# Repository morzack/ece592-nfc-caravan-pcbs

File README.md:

# ece592-nfc-caravan-pcbs

submodules vendor in reference boards for tt06 and caravel.

most up-to-date caravel evaluation PCB at `caravel_board/hardware/development/caravel-dev-v5-M.2` -- this contains details on FTDI module and flash memory for bringup of on-chip VexRiscv management CPU

## work breakdown

following a top-down design

1. make symbol for pinout (actual)
2. identify routing constaints for breakout
3. make block diagram of off-chip requirements for bringup
4. implement schematics for off-chip stuff
5. layout, etc

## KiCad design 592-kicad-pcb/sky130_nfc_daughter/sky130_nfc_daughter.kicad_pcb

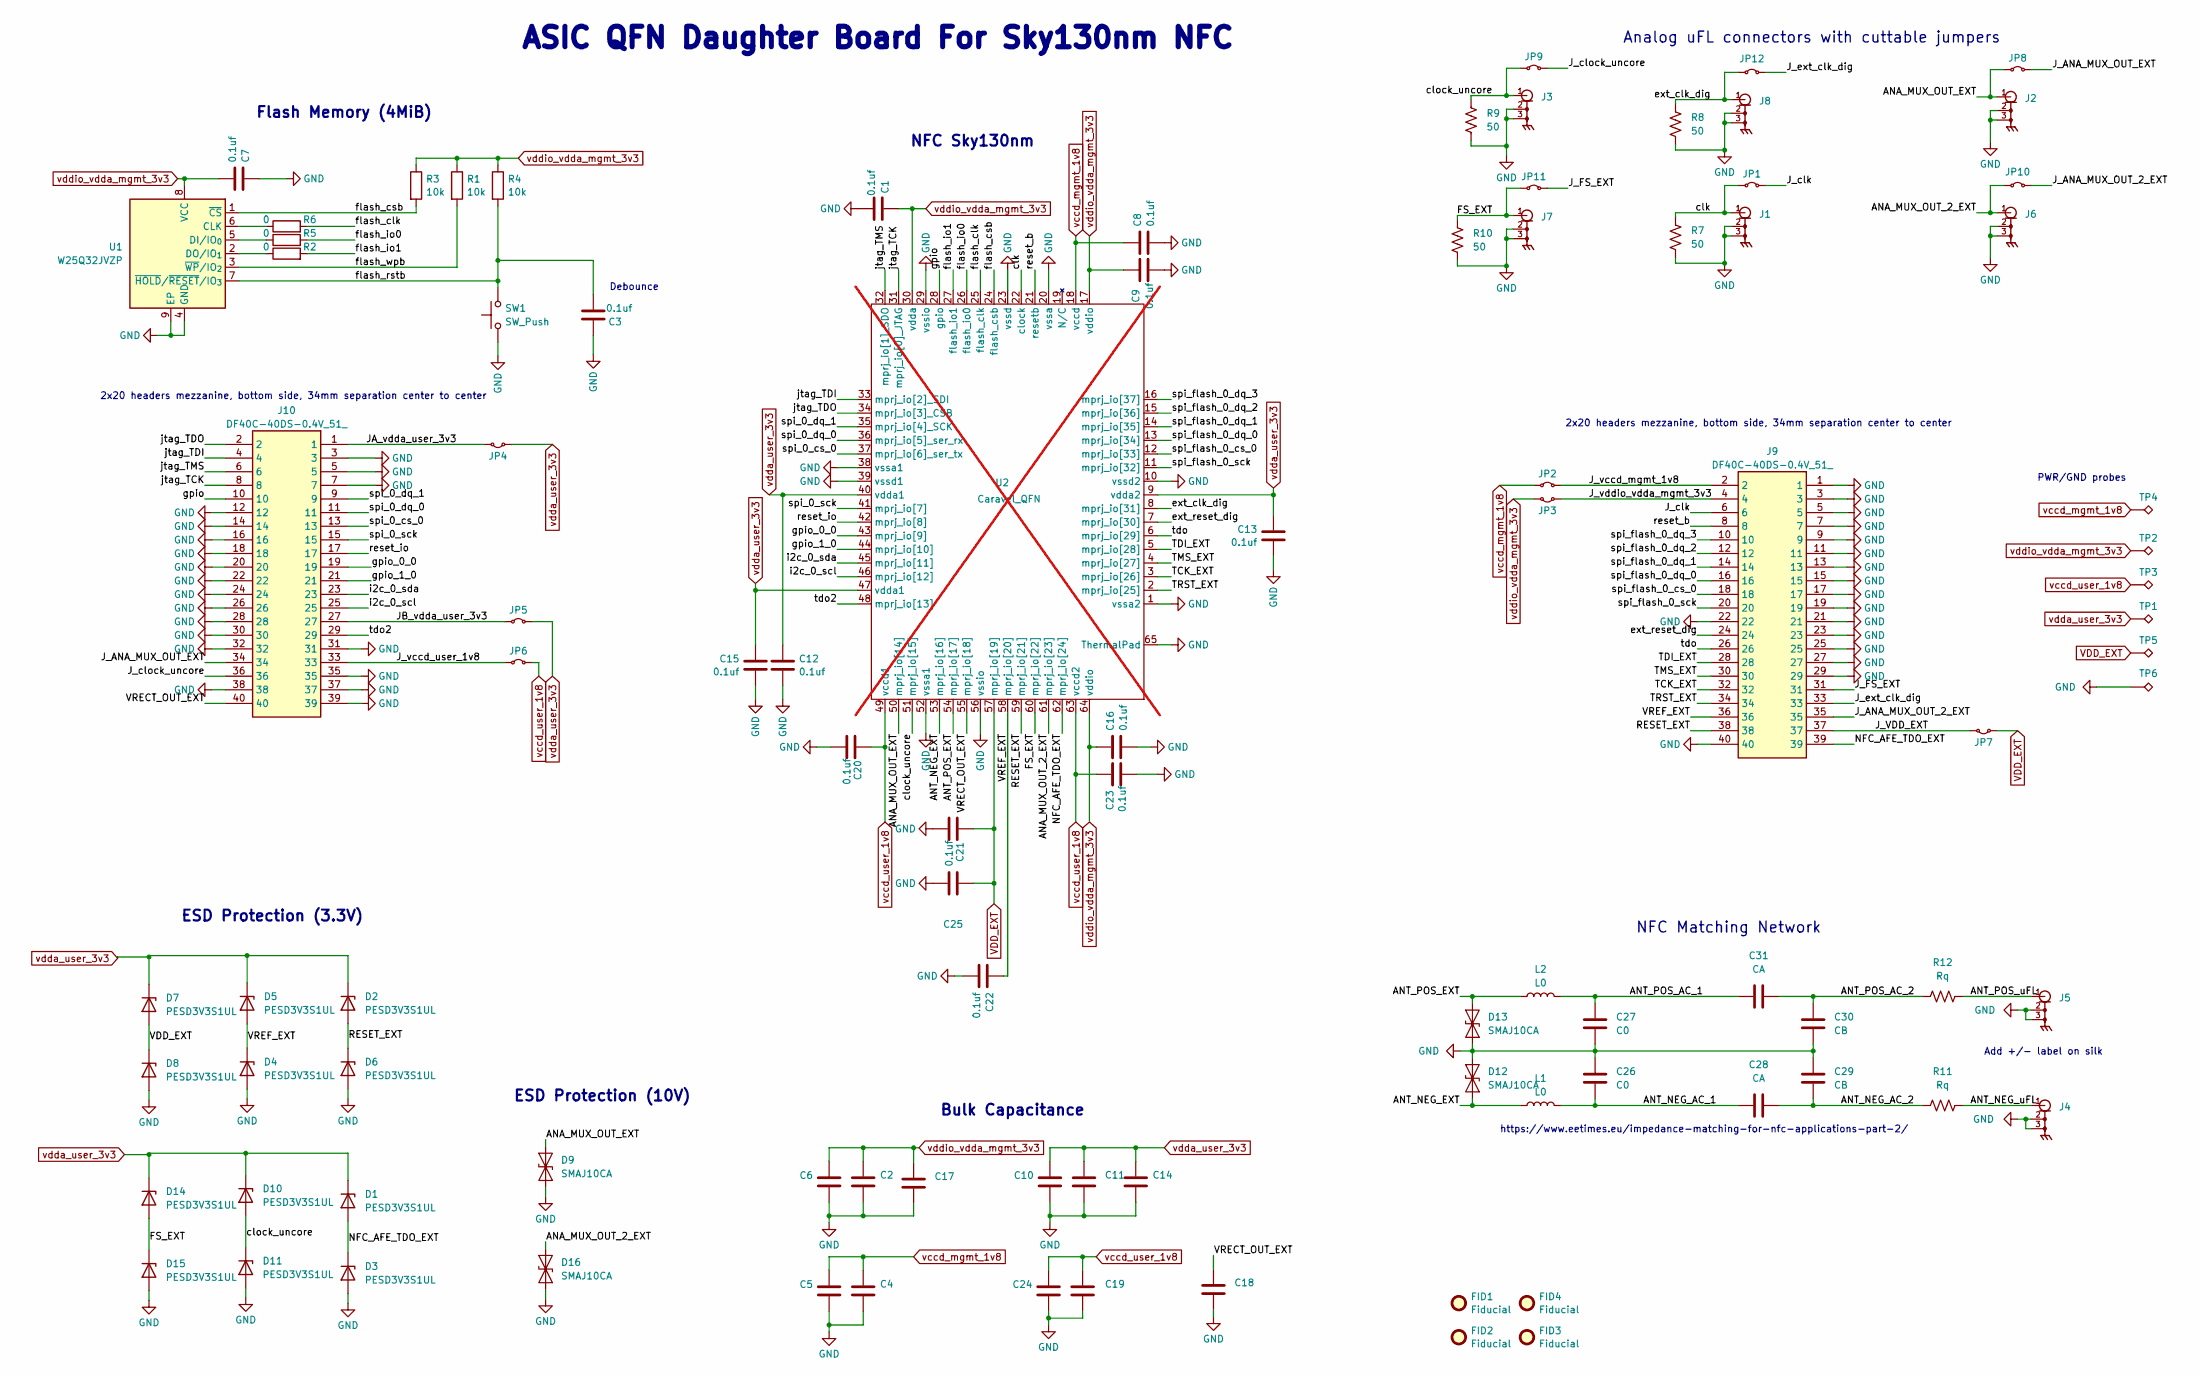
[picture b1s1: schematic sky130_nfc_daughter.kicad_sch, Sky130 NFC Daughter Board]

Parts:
C1, C3, C7, C8, C9, C12, C13, C15, C16, C20, C21, C22, C23: 0.1uf; C_0402_1005Metric
C2, C4, C5, C6, C10, C11, C14, C17, C18, C19, C24, C25: C_1u_0603_50V; C_0603_1608Metric
C26, C27: C0; C_0603_1608Metric_Pad1.08x0.95mm_HandSolder
C28, C31: CA; C_0603_1608Metric_Pad1.08x0.95mm_HandSolder
C29, C30: CB; C_0603_1608Metric_Pad1.08x0.95mm_HandSolder
D1, D2, D3, D4, D5, D6, D7, D8, D10, D11, D14, D15: PESD3V3S1UL; D_SOD-882
D9, D12, D13, D16: SMAJ10CA; D_SMA
FID1, FID2, FID3, FID4: Fiducial; Fiducial_1mm_Mask2mm
J1, J2, J3, J4, J5, J6, J7, J8: U.FL-R-SMT-1_80_; UFLRSMT180
J9, J10: DF40C-40DS-0.4V_51_; DF40C40DS04V51
JP1, JP2, JP3, JP4, JP5, JP6, JP7, JP8, JP9, JP10, JP11, JP12: Jumper_2_Small_Bridged; SolderJumper-2_P1.3mm_Bridged_RoundedPad1.0x1.5mm
L1, L2: L0; L_0603_1608Metric_Pad1.05x0.95mm_HandSolder
R1, R3, R4: 10k; R_0402_1005Metric
R2, R5, R6: 0; R_0402_1005Metric
R7, R8, R9, R10: 50; R_0402_1005Metric
R11, R12: Rq; R_0603_1608Metric_Pad0.98x0.95mm_HandSolder
SW1: SW_Push; SW_Push_1P1T_XKB_TS-1187A
TP1, TP2, TP3, TP4, TP5, TP6: TestPoint_Alt; TestPoint_Keystone_5019_Minature; MPN 5019; DigikeyPN 36-5019CT-ND
U1: W25Q32JVZP; WSON-8-1EP_6x5mm_P1.27mm_EP3.4x4.3mm
U2: Caravel_QFN; QFN-64-1EP_9x9mm_P0.5mm_EP7.65x7.65mm_SMALL_EPAD; not fitted

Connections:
/ANA_MUX_OUT_2_EXT: D16.2 (A2), J6.1, JP10.1 (A), U2.61 (mprj_io[23])
/ANA_MUX_OUT_EXT: D9.2 (A2), J2.1, JP8.1 (A), U2.50 (mprj_io[14])
/ANT_NEG_AC_1: C26.2, C28.1, L1.2
/ANT_NEG_AC_2: C28.2, C29.2, R11.1
/ANT_NEG_EXT: D12.2 (A2), L1.1, U2.53 (mprj_io[16])
/ANT_NEG_uFL: J4.1, R11.2
/ANT_POS_AC_1: C27.1, C31.1, L2.2
/ANT_POS_AC_2: C30.1, C31.2, R12.1
/ANT_POS_EXT: D13.2 (A2), L2.1, U2.54 (mprj_io[17])
/ANT_POS_uFL: J5.1, R12.2
/FS_EXT: D14.2 (A), D15.1 (K), J7.1, JP11.1 (A), R10.2, U2.60 (mprj_io[22])
/JA_vdda_user_3v3: J10.1, JP4.1 (A)
/JB_vdda_user_3v3: J10.27, JP5.2 (B)
/J_ANA_MUX_OUT_2_EXT: J9.35, JP10.2 (B)
/J_ANA_MUX_OUT_EXT: J10.34, JP8.2 (B)
/J_FS_EXT: J9.31, JP11.2 (B)
/J_VDD_EXT: J9.37, JP7.1 (A)
/J_clk: J9.6, JP1.2 (B)
/J_clock_uncore: J10.36, JP9.2 (B)
/J_ext_clk_dig: J9.33, JP12.2 (B)
/J_vccd_mgmt_1v8: J9.2, JP2.1 (A)
/J_vccd_user_1v8: J10.33, JP6.2 (B)
/J_vddio_vdda_mgmt_3v3: J9.4, JP3.1 (A)
/NFC_AFE_TDO_EXT: D1.2 (A), D3.1 (K), J9.39, U2.62 (mprj_io[24])
/RESET_EXT: D2.2 (A), D6.1 (K), J9.38, U2.59 (mprj_io[21])
/TCK_EXT: J9.32, U2.3 (mprj_io[26])
/TDI_EXT: J9.28, U2.5 (mprj_io[28])
/TMS_EXT: J9.30, U2.4 (mprj_io[27])
/TRST_EXT: J9.34, U2.2 (mprj_io[25])
/VRECT_OUT_EXT: C18.1, J10.40, U2.55 (mprj_io[18])
/VREF_EXT: C22.1, D4.1 (K), D5.2 (A), J9.36, U2.58 (mprj_io[20])
/clk: J1.1, JP1.1 (A), R7.2, U2.22 (clock)
/clock_uncore: D10.2 (A), D11.1 (K), J3.1, JP9.1 (A), R9.2, U2.51 (mprj_io[15])
/ext_clk_dig: J8.1, JP12.1 (A), R8.2, U2.8 (mprj_io[31])
/ext_reset_dig: J9.24, U2.7 (mprj_io[30])
/flash_clk: R6.2, U2.25 (flash_clk)
/flash_csb: R3.2, U1.1 (~CS), U2.24 (flash_csb)
/flash_io0: R5.2, U2.26 (flash_io0)
/flash_io1: R2.2, U2.27 (flash_io1)
/flash_rstb: C3.1, R4.2, SW1.2, U1.7 (~HOLD/~RESET/IO_{3})
/flash_wpb: R1.2, U1.3 (~WP/IO_{2})
/gpio: J10.10, U2.28 (gpio)
/gpio_0_0: J10.19, U2.43 (mprj_io[9])
/gpio_1_0: J10.21, U2.44 (mprj_io[10])
/i2c_0_scl: J10.25, U2.46 (mprj_io[12])
/i2c_0_sda: J10.23, U2.45 (mprj_io[11])
/jtag_TCK: J10.8, U2.31 (mprj_io[0]_JTAG)
/jtag_TDI: J10.4, U2.33 (mprj_io[2]_SDI)
/jtag_TDO: J10.2, U2.34 (mprj_io[3]_CSB)
/jtag_TMS: J10.6, U2.32 (mprj_io[1]_SDO)
/reset_b: J9.8, U2.21 (resetb)
/reset_io: J10.17, U2.42 (mprj_io[8])
/spi_0_cs_0: J10.13, U2.37 (mprj_io[6]_ser_tx)
/spi_0_dq_0: J10.11, U2.36 (mprj_io[5]_ser_rx)
/spi_0_dq_1: J10.9, U2.35 (mprj_io[4]_SCK)
/spi_0_sck: J10.15, U2.41 (mprj_io[7])
/spi_flash_0_cs_0: J9.18, U2.12 (mprj_io[33])
/spi_flash_0_dq_0: J9.16, U2.13 (mprj_io[34])
/spi_flash_0_dq_1: J9.14, U2.14 (mprj_io[35])
/spi_flash_0_dq_2: J9.12, U2.15 (mprj_io[36])
/spi_flash_0_dq_3: J9.10, U2.16 (mprj_io[37])
/spi_flash_0_sck: J9.20, U2.11 (mprj_io[32])
/tdo: J9.26, U2.6 (mprj_io[29])
/tdo2: J10.29, U2.48 (mprj_io[13])
GND: C1.1, C2.2, C3.2, C4.2, C5.2, C6.2, C7.1, C8.1, C9.1, C10.2, C11.2, C12.2, C13.1, C14.2, C15.2, C16.1, C17.2, C18.2, C19.2, C20.2, C21.2, C22.2, C23.1, C24.2, C25.1, C26.1, C27.2, C29.1, C30.2, D3.2 (A), D4.2 (A), D6.2 (A), D8.2 (A), D9.1 (A1), D11.2 (A), D12.1 (A1), D13.1 (A1), D15.2 (A), D16.1 (A1), J1.2, J1.3, J2.2, J2.3, J3.2, J3.3, J4.2, J4.3, J5.2, J5.3, J6.2, J6.3, J7.2, J7.3, J8.2, J8.3, J9.1, J9.3, J9.5, J9.7, J9.9, J9.11, J9.13, J9.15, J9.17, J9.19, J9.21, J9.22, J9.23, J9.25, J9.27, J9.29, J9.40, J10.3, J10.5, J10.7, J10.12, J10.14, J10.16, J10.18, J10.20, J10.22, J10.24, J10.26, J10.28, J10.30, J10.31, J10.32, J10.35, J10.37, J10.38, J10.39, R7.1, R8.1, R9.1, R10.1, SW1.1, TP6.1, U1.4 (GND), U1.9 (EP), U2.1 (vssa2), U2.10 (vssd2), U2.20 (vssa), U2.23 (vssd), U2.29 (vssio), U2.38 (vssa1), U2.39 (vssd1), U2.52 (vssa1), U2.56 (vssio), U2.65 (ThermalPad); also elsewhere on the board
unnamed: R6.1, U1.6 (CLK)
unnamed: R5.1, U1.5 (DI/IO_{0})
unnamed: R2.1, U1.2 (DO/IO_{1})
VDD_EXT: C21.1, C25.2, D7.2 (A), D8.1 (K), JP7.2 (B), TP5.1, U2.57 (mprj_io[19])
vccd_mgmt_1v8: C4.1, C5.1, C8.2, JP2.2 (B), TP4.1, U2.18 (vccd)
vccd_user_1v8: C19.1, C20.1, C23.2, C24.1, JP6.1 (A), TP3.1, U2.49 (vccd1), U2.63 (vccd2)
vdda_user_3v3: C10.1, C11.1, C12.1, C13.2, C14.1, C15.1, D1.1 (K), D2.1 (K), D5.1 (K), D7.1 (K), D10.1 (K), D14.1 (K), JP4.2 (B), JP5.1 (A), TP1.1, U2.9 (vdda2), U2.40 (vdda1), U2.47 (vdda1)
vddio_vdda_mgmt_3v3: C1.2, C2.1, C6.1, C7.2, C9.2, C16.2, C17.1, JP3.2 (B), R1.1, R3.1, R4.1, TP2.1, U1.8 (VCC), U2.17 (vddio), U2.30 (vdda), U2.64 (vddio)

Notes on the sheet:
ESD Protection (10V)
2x20 headers mezzanine, bottom side, 34mm separation center to center
https://www.eetimes.eu/impedance-matching-for-nfc-applications-part-2/
ASIC QFN Daughter Board For Sky130nm NFC
NFC Sky130nm
PWR/GND probes
Flash Memory (4MiB)
Debounce
Bulk Capacitance
NFC Matching Network
ESD Protection (3.3V)
Analog uFL connectors with cuttable jumpers
Add +/- label on silk

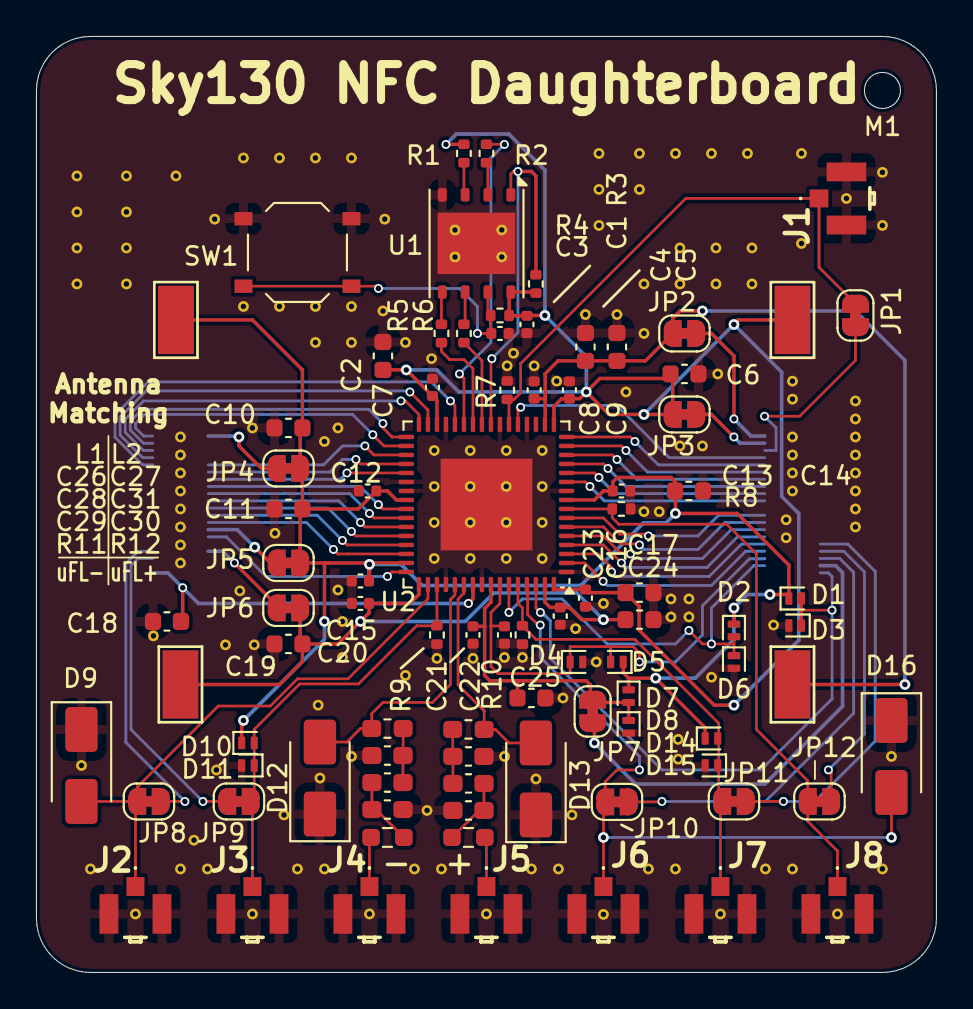
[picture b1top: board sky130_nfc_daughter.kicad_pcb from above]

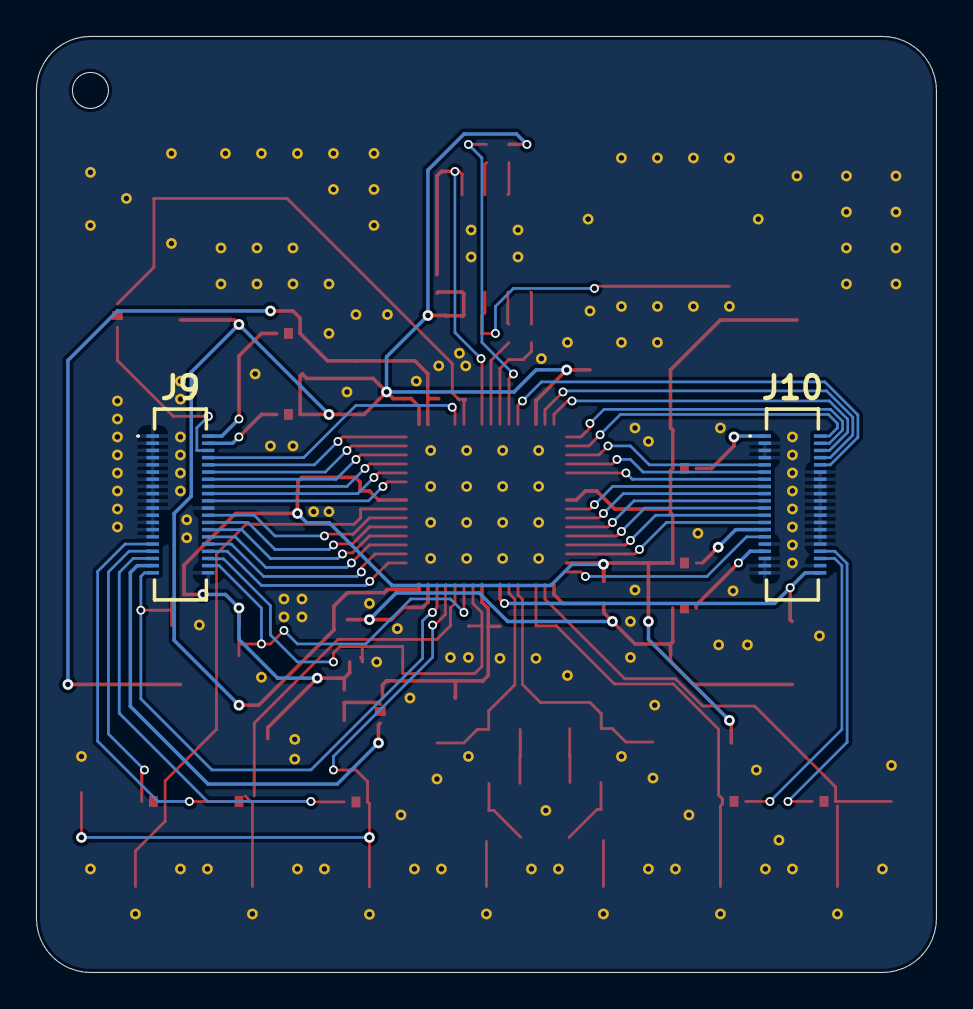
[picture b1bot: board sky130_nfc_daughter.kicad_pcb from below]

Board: 4 copper layers, 50.0 x 52.0 mm, 96 parts (2 on the bottom side), 73 nets.

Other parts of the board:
M1: MountingHole_2mm
STITCHM1, STITCHM2, STITCHM3, STITCHM4, STITCHM5: STITCHING_VIA_0p3mm

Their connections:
GND: STITCHM1.1, STITCHM2.1, STITCHM3.1, STITCHM4.1, STITCHM5.1; also elsewhere on the board

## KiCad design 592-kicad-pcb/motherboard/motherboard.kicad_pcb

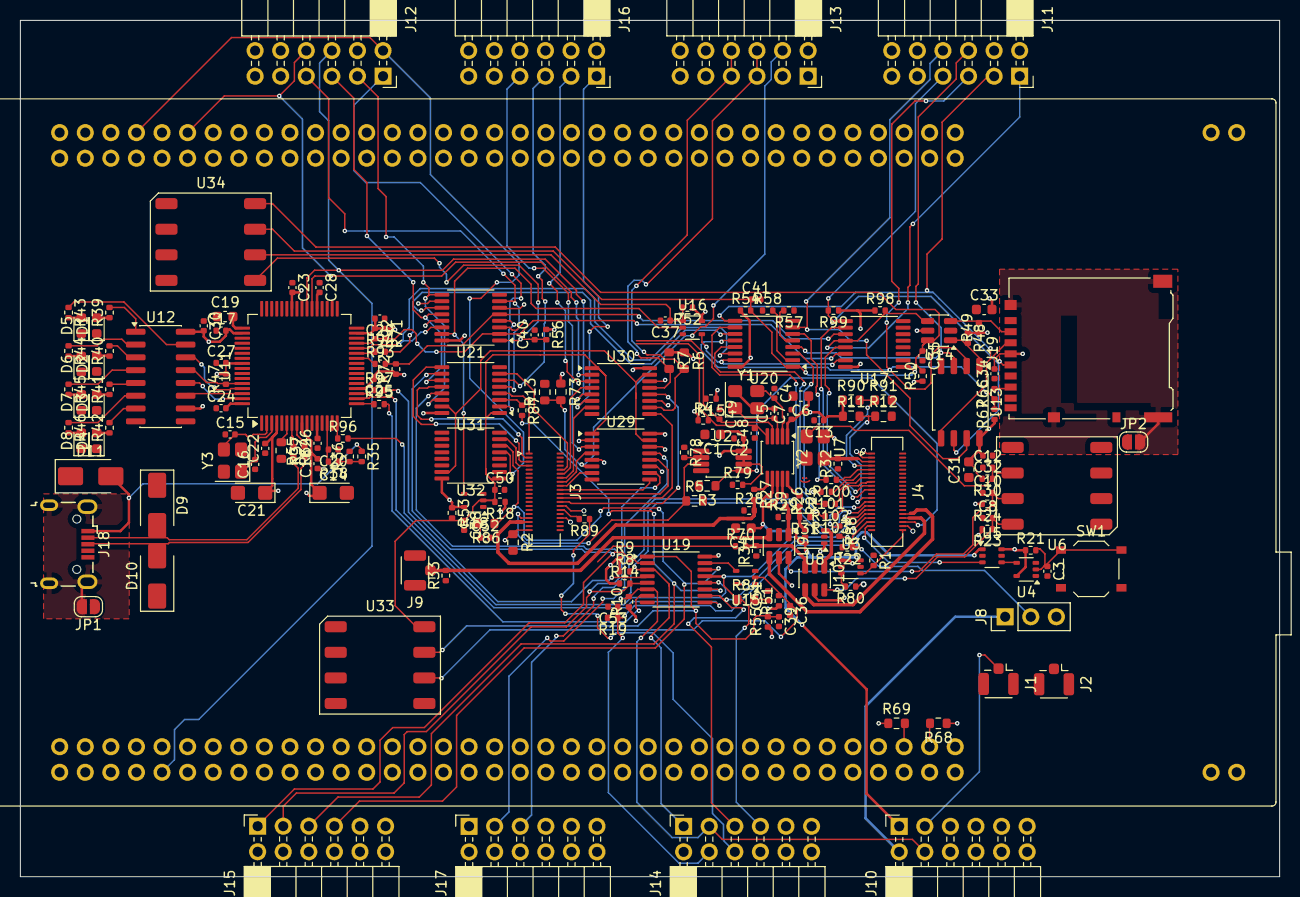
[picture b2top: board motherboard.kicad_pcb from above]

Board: 4 copper layers, 125.0 x 85.0 mm, 194 parts (0 on the bottom side), 176 nets.

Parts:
C1, C6, C11, C31, C33: 1u; C_0603_1608Metric
C2, C3, C7, C8, C9, C10, C12, C17, C18, C22, C23, C24, C25, C26, C27, C28, C29, C30, C32, C34, C35, C36, C37, C38, C39, C40, C41, C50: 100n; C_0402_1005Metric
C4, C5: 16p; C_0402_1005Metric
C13, C20, C53: 10n; C_0402_1005Metric
C14, C21: 4.7u; CP_EIA-3216-18_Kemet-A
C15, C16: 10p; C_0402_1005Metric
C19: 3.3u; C_0603_1608Metric
C48, C49: 0; C_0402_1005Metric
C51, C52: 100p; C_0402_1005Metric
D1, D2, D3, D4: d_white; D_0603_1608Metric
D5, D6, D7, D8: d_red; D_0603_1608Metric
D9, D10, D11: SMAJ10CA; D_SMA
J1, J2, J9: U.FL; U.FL_Hirose_U.FL-R-SMT-1_Vertical
J3, J4: DF40C-40DP-0.4V(51); Hirose_DF40C(2.0)-40DS-0.4V_2x20_P0.4mm
J8: 2.54mm jumper; PinHeader_1x03_P2.54mm_Vertical
J10, J11, J12, J13, J14, J15, J16, J17: Conn_02x06_Odd_Even; PinSocket_2x06_P2.54mm_Horizontal
J18: USB_B_Micro; USB_Micro-B_Wuerth_629105150521
J19: Micro_SD_Card; microSD_HC_Hirose_DM3AT-SF-PEJM5
JP1, JP2: solderjump; SolderJumper-2_P1.3mm_Open_RoundedPad1.0x1.5mm
R1: 1M; R_0402_1005Metric
R2, R3, R5: 10M; R_0603_1608Metric
R4, R15: 5k; R_0402_1005Metric
R6, R7: 2k; R_0603_1608Metric
R8, R9, R10, R14, R18, R19, R21, R23, R24, R28, R29, R30, R31, R32, R33, R34, R36, R47, R50, R51, R52, R53, R54, R55, R56, R57, R58, R67, R71, R72, R92, R98, R99: 10k; R_0402_1005Metric
R11, R12, R13, R73, R90, R91: 10k; R_0603_1608Metric
R22, R48, R49: 100k; R_0402_1005Metric
R25, R26, R27: 10; R_0402_1005Metric
R35: 4.7k; R_0402_1005Metric
R37: 12k <1%; R_0603_1608Metric
R38: 1k; R_0402_1005Metric
R39, R40, R41, R42: 150; R_0402_1005Metric
R43, R44, R45, R46: 330; R_0402_1005Metric
R64, R65, R70, R87, R88, R89, R100, R101, R102, R103: 0; R_0402_1005Metric
R66: 27; R_0402_1005Metric
R68, R69: 5k; R_0603_1608Metric
R78, R79, R80: 100; R_0402_1005Metric
R84, R86: 75; R_0603_1608Metric
R93, R94, R95, R96, R97: 22; R_0402_1005Metric
SW1: C318884; SW_Push_1P1T_XKB_TS-1187A
U1: NUCLEO144-H743ZI; ST_Morpho_Connector_144_STLink
U2: OPA2328DGKR; VSSOP-8_3x3mm_P0.65mm
U3, U5, U8: 74LVC1T45GW; SOT-363_SC-70-6
U4, U15, U18: SN74LVC1G14DBV; SOT-353_SC-70-5
U6, U33, U34: SMXS-04K; SMXS-04K-TP
U7: SX3M10.000B10F20TNN; Crystal_SMD_3225-4Pin_3.2x2.5mm
U9, U10, U14: SN74LVC1G3157DBVR; SOT-23-6
U11: FT4232H; LQFP-64_10x10mm_P0.5mm
U12: 74HC595; SOIC-16_3.9x9.9mm_P1.27mm
U13: W25Q32JVSS; SOIC-8_5.3x5.3mm_P1.27mm
U16: SN74LVC1G00DCK; SOT-353_SC-70-5
U17, U19, U20, U21, U29, U30, U31, U32: 74CBTLV3257PW,118; TSSOP-16_4.4x5mm_P0.65mm
Y1: NX3225GA-25.000M-STD-CRG-2; Crystal_SMD_3225-4Pin_3.2x2.5mm
Y2: Si5351A; MSOP-10_3x3mm_P0.5mm
Y3: X322512MSB4SI; Crystal_SMD_3225-4Pin_3.2x2.5mm

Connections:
+1V8: C9.1, C11.1, J10.1, U3.6 (VCCB), U5.1 (VCCA), U8.6 (VCCB), Y2.7 (VDDO)
+3V3: C1.1, C2.1, C6.1, C7.1, C13.1, C14.1, C17.2, C18.2, C21.1, C22.2, C23.2, C25.2, C27.2, C29.2, C30.2, C31.2, C32.2, C33.2, C34.2, J10.11, J10.12, J11.11, J11.12, J12.11, J12.12, J13.11, J13.12, J14.11, J14.12, J15.11, J15.12, J16.11, J16.12, J17.11, J17.12, J19.4 (VDD), R4.1, R6.1, R7.1, R8.1, R9.1, R10.1, R11.1, R14.1, R15.1, R18.1, R21.1, R23.2, R24.2, R30.2, R47.2, R48.1, R49.1, R50.1, R51.1, R52.1, R53.1, R54.1, R55.1, R56.1, R67.1, R68.1, R69.1, R71.1, R72.1, R73.1, R90.1, R92.1, R98.1, R99.1, U2.8 (Vdd), U3.1 (VCCA), U4.5 (VCC), U5.6 (VCCB), U7.4 (VDD), U8.1 (VCCA), U9.5 (VCC), U10.5 (VCC), U11.4 (VPHY), U11.9 (VPLL), U11.20 (VCCIO), U11.31 (VCCIO), U11.42 (VCCIO), U11.50 (VREGIN), U11.56 (VCCIO), U12.10 (~SRCLR), U12.16 (VCC), U13.8 (VCC), U14.5 (VCC), U15.5 (VCC), U16.5 (VCC), U17.16 (VCC), U18.5 (VCC), U19.16 (VCC), U20.16 (VCC), U21.16 (VCC), U29.16 (VCC), U30.16 (VCC), U31.16 (VCC), U32.16 (VCC), Y2.1 (VDD)
/PA0_UART4_RX: U1.28 (PA0), U11.48 (DDBUS0)
/PA1_UART4_TX: U1.30 (ETH_REF_CLK/PA1), U11.52 (DDBUS1)
/PA4_DAC_OUT1: J8.3, U1.32 (PA4)
/PB8_I2C4_SCL: C49.2, R15.2, R68.2, U1.75 (PB8), Y2.4 (SCL)
/PB9_I2C4_SDA: C48.2, R4.2, R69.2, U1.77 (PB9), Y2.5 (SDA)
/PB14_TIM12_CH1: R70.1, U1.100 (LD3/PB14)
/PD7: U1.45 (PD7), U30.14
/PE0_UART8_RX: J12.6, U1.136 (PE0), U11.39 (CDBUS1), U30.5
/PE1_UART8_TX: J12.8, U1.61 (PE1), U11.38 (CDBUS0), U30.2
/PF6_SPI5_CS: U1.9 (PF6), U21.3
/PF7_SPI5_SCK: U1.11 (PF7), U21.6
/PF8_SPI5_MISO: U1.54 (PF8), U21.13
/PF9_SPI5_MOSI: U1.56 (PF9), U21.10
/PG0: U1.59 (PG0), U29.14
/PG1: U1.58 (PG1), U30.11
/PG9: U1.63 (PG9), U29.11
/PG10: U1.66 (PG10), U29.2
/PG12: J12.2, U1.65 (PG12), U32.5
/PG15: U1.64 (PG15), U29.5
/motherboard_top/ADC_chip_ana_mux_out_1: J1.1 (In), J10.3, R78.1
/motherboard_top/ADC_chip_ana_mux_out_2: J2.1 (In), J10.5, R79.1
/motherboard_top/GPIO_JTAG_FTDI_source_select: C39.1, R55.2, U19.1 (S), U33.7 (2o)
/motherboard_top/GPIO_MGMT_enable: C38.1, C50.1, R18.2, R53.2, U18.2, U29.1 (S), U30.1 (S), U31.1 (S), U32.1 (S), U33.8 (1o)
/motherboard_top/GPIO_SPI_MGMT_source_sel: C40.1, R56.2, U21.1 (S), U34.5 (4o)
/motherboard_top/GPIO_chip_nfc_afe_tdo_ext: J10.7, R80.1
/motherboard_top/GPIO_chip_nfc_ext_reset_dig: J4.23, J10.6, R11.2, R12.1
/motherboard_top/GPIO_chip_nfc_jtag_tdo: J14.5, R88.2, U19.10
/motherboard_top/GPIO_chip_nfc_jtag_tdo2: J14.6, R89.1
/motherboard_top/GPIO_chip_rck_reset_io: J13.4, R13.1, R73.2, U29.6
/motherboard_top/GPIO_ftdi_jtag_src_en: C36.1, R51.2, U15.2, U33.6 (3o)
/motherboard_top/GPIO_rck_mem_sel_sdB: C35.1, R50.2, U14.6 (S), U34.8 (1o)
/motherboard_top/GPIO_rck_mem_source_en: C37.1, R52.2, U16.1, U34.6 (3o)
/motherboard_top/GPIO_rck_mem_source_sel_ftdiB: C41.1, R54.2, U17.1 (S), U20.1 (S), U34.7 (2o)
/motherboard_top/ana_buffers/a1: R78.2, U2.1 (Vout1), U2.2 (Vin1m)
/motherboard_top/ana_buffers/a2: R79.2, U2.6 (Vin2m), U2.7 (Vout2)
/motherboard_top/anamisc_vref_ext_in: J8.1, J10.2
/motherboard_top/chip_connection/mprj_io_0: J3.7, U32.7
/motherboard_top/chip_connection/mprj_io_1: J3.5, U31.9
/motherboard_top/chip_connection/mprj_io_2: J3.3, U31.12
/motherboard_top/chip_connection/mprj_io_3: J3.1, U31.4
/motherboard_top/chip_connection/mprj_io_4: J3.10, U31.7
/motherboard_top/chip_connection/mprj_io_5: J3.12, U30.4
/motherboard_top/chip_connection/mprj_io_6: J3.14, U30.7
/motherboard_top/chip_connection/mprj_io_7: J3.16, U29.4
/motherboard_top/chip_connection/mprj_io_8: J3.18, U29.7
/motherboard_top/chip_connection/mprj_io_9: J3.20, U29.9
/motherboard_top/chip_connection/mprj_io_10: J3.22, U29.12
/motherboard_top/chip_connection/mprj_io_11: J3.24, U30.9
/motherboard_top/chip_connection/mprj_io_12: J3.26, U30.12
/motherboard_top/chip_connection/resetb: J4.7, R90.2, R91.1
/motherboard_top/chip_connection/user_3v3: J3.2, J3.28
/motherboard_top/chip_nfc_ana_mux_out: J3.33, R5.1, U2.3 (Vin1p)
/motherboard_top/chip_nfc_ana_mux_out_2: J4.36, R3.1, U2.5 (Vin2p)
/motherboard_top/chip_nfc_ext_clk_dig: J4.34, U10.4 (A)
/motherboard_top/chip_nfc_fs: J4.32, U9.4 (A)
/motherboard_top/chip_nfc_jtag_tck: J4.31, J14.7, R84.1, U19.13
/motherboard_top/chip_nfc_jtag_tdi: J4.27, J10.4, J14.3, R10.2, U19.6
/motherboard_top/chip_nfc_jtag_tms: J4.29, J14.1, R8.2, U19.3
/motherboard_top/chip_nfc_jtag_trst: C53.1, J4.33, J14.4, R19.1
/motherboard_top/chip_nfc_nfc_afe_tdo: J4.40, R1.2, U3.4 (B)
/motherboard_top/chip_nfc_reset: J4.37, U5.3 (A)
/motherboard_top/chip_nfc_vrect_out: J3.39, J10.8, R2.1
/motherboard_top/chip_nfc_vref: J4.35, J8.2, R22.1
/motherboard_top/chip_rck_clock_uncore: J3.35, R27.2, R28.2
/motherboard_top/chip_rck_gpio_0_0: J17.5, U29.10
/motherboard_top/chip_rck_gpio_1_0: J17.3, U29.13
/motherboard_top/chip_rck_i2c_scl: J13.5, J13.6, R7.2, U30.13
/motherboard_top/chip_rck_i2c_sda: J13.7, J13.8, R6.2, U30.10
/motherboard_top/chip_rck_jtag_tck: J15.7, R86.1, U19.14, U32.6
/motherboard_top/chip_rck_jtag_tdi: J15.3, R14.2, U19.5, U31.13
/motherboard_top/chip_rck_jtag_tdo: J15.5, R87.2, U19.11
/motherboard_top/chip_rck_jtag_tms: J15.1, R9.2, U19.2, U31.10
/motherboard_top/chip_rck_spi_0_cs_0: J16.1, U30.6
/motherboard_top/chip_rck_spi_0_dq_0_mosi: J16.3, U30.3
/motherboard_top/chip_rck_spi_0_dq_1_miso: J16.5, U31.6
/motherboard_top/chip_rck_spi_0_sck: J16.7, U29.3
/motherboard_top/chip_spi_flash_0_cs_0: J4.17, U17.13
/motherboard_top/chip_spi_flash_0_dq_0: R103.2, U20.10
/motherboard_top/chip_spi_flash_0_dq_1: R102.2, U20.13
/motherboard_top/chip_spi_flash_0_dq_2: R101.2, U20.3
/motherboard_top/chip_spi_flash_0_dq_3: R100.2, U20.6
/motherboard_top/chip_spi_flash_0_sck: J4.19, U17.10
/motherboard_top/chip_support_misc/GPIO_RESET_EXT: C3.1, R21.2, SW1.1 (A), U4.2
/motherboard_top/clock_sources/CARAVEL_CLK_EN: C12.2, R30.1, U6.6 (3o), U7.1 (OE)
/motherboard_top/clock_sources/EXT_CLK_DIG_SEL: C8.2, R23.1, U6.8 (1o), U10.6 (S)
/motherboard_top/clock_sources/FS_EXT_SEL: C10.2, R24.1, U6.7 (2o), U9.6 (S)
/motherboard_top/clock_sources/ext_clk_dig_gen: R25.2, R31.2, U8.4 (B)
/motherboard_top/clock_sources/fs_ext_aux: J9.1 (In), R33.2, U9.3 (B1)
/motherboard_top/clock_sources/fs_ext_gen: R26.2, R29.2, U9.1 (B2)
/motherboard_top/ftdi1_jtag_tck: R96.2, U19.12
/motherboard_top/ftdi1_jtag_tdi: R95.2, U19.7
/motherboard_top/ftdi1_jtag_tdo: U11.18 (ADBUS2), U19.9
/motherboard_top/ftdi1_jtag_tms: R97.2, U19.4
/motherboard_top/ftdi/FTDI_RESETb: C20.2, R38.2, U11.14 (~RESET)
/motherboard_top/ftdi/USB_DM: D9.2 (A2), J18.2 (D-), R64.2
/motherboard_top/ftdi/USB_DP: D10.2 (A2), J18.3 (D+), R65.1
/motherboard_top/ftdi/ftdi_1v8: C19.2, C24.2, C26.2, C28.2, U11.12 (VCORE), U11.37 (VCORE), U11.49 (VREGOUT), U11.64 (VCORE)
/motherboard_top/ftdi/ftdi_eeclk: U11.62 (EECLK), U12.11 (SRCLK)
/motherboard_top/ftdi/ftdi_eecs: U11.63 (EECS), U12.12 (RCLK)
/motherboard_top/ftdi/ftdi_eedata: U11.61 (EEDATA), U12.14 (SER)
/motherboard_top/ftdi/ftdi_pwren: R47.1, U11.60 (~PWREN), U12.13 (~OE)
/motherboard_top/ftdi_jtag_src_enB: U15.4, U19.15 (~OE)
/motherboard_top/ftdi_spi_cs: R71.2, R92.2, U11.29 (BDBUS3), U17.14, U21.2
/motherboard_top/ftdi_spi_miso: U11.28 (BDBUS2), U20.14, U21.14
/motherboard_top/ftdi_spi_mosi: R94.2, U20.11, U21.11
/motherboard_top/ftdi_spi_sck: R72.2, R93.2, U17.11, U21.5
/motherboard_top/memory/nor_cs: R48.2, U13.1 (~CS), U14.1 (B2)
/motherboard_top/memory/sd_cs: J19.2 (DAT3/CD), R49.2, U14.3 (B1)
/motherboard_top/mgmt_clk: J4.5, R32.2, U7.3 (OUT)
/motherboard_top/mgmt_csb: J12.1, U21.4, U31.2
/motherboard_top/mgmt_sck: J12.7, U21.7, U31.5
/motherboard_top/mgmt_sdi: J12.3, U21.9, U31.14
/motherboard_top/mgmt_sdo: J12.5, U21.12, U31.11
/motherboard_top/rck_mem_cs: J11.1, R98.2, U14.4 (A), U17.12
/motherboard_top/rck_mem_io2: J11.6, U13.3 (~WP/IO_{2}), U20.4
/motherboard_top/rck_mem_io3: J11.8, U13.7 (~HOLD/~RESET/IO_{3}), U20.7
/motherboard_top/rck_mem_miso_i01: J11.5, R66.1, R67.2, U13.2 (DO/IO_{1}), U20.12
/motherboard_top/rck_mem_mosi_io0: J11.3, J19.3 (CMD), U13.5 (DI/IO_{0}), U20.9
/motherboard_top/rck_mem_sck: J11.7, J19.5 (CLK), R99.2, U13.6 (CLK), U17.9
/motherboard_top/rck_mem_source_enB: U16.4, U17.15 (~OE), U20.15 (~OE)
/motherboard_top/spi_mgmt_enb: U16.2, U18.4, U21.15 (~OE)
GND: C1.2, C2.2, C3.2, C4.1, C5.2, C6.2, C7.2, C8.1, C9.2, C10.1, C11.2, C12.1, C13.2, C14.2, C15.1, C16.1, C17.1, C18.1, C19.1, C20.1, C21.2, C22.1, C23.1, C24.1, C25.1, C26.1, C27.1, C28.1, C29.1, C30.1, C31.1, C32.1, C33.1, C34.1, C35.2, C36.2, C37.2, C38.2, C39.2, C40.2, C41.2, C48.1, C49.1, C50.2, C51.2, C52.2, C53.2, D1.1 (K), D2.1 (K), D3.1 (K), D4.1 (K), D5.1 (K), D6.1 (K), D7.1 (K), D8.1 (K), D9.1 (A1), D10.1 (A1), D11.1 (A1), J1.2 (Ext), J2.2 (Ext), J3.4, J3.6, J3.8, J3.11, J3.13, J3.15, J3.17, J3.19, J3.21, J3.23, J3.25, J3.27, J3.29, J3.31, J3.32, J3.36, J3.37, J3.38, J3.40, J4.2, J4.4, J4.6, J4.8, J4.10, J4.12, J4.14, J4.16, J4.18, J4.20, J4.21, J4.22, J4.24, J4.26, J4.28, J4.30, J4.39, J9.2 (Ext), J10.9, J10.10, J11.9, J11.10, J12.9, J12.10, J13.2, J13.9, J13.10, J14.9, J14.10, J15.9, J15.10, J16.9, J16.10, J17.9, J17.10, J18.5 (GND), J19.6 (VSS), JP1.1 (A), JP2.1 (A), R1.1, R2.2, R3.2, R5.2, R12.2, R13.2, R19.2, R22.2, R28.1, R29.1, R31.1, R32.1, R33.1, R34.1, R36.2, R37.2, R57.1, R58.1, R91.2, SW1.2 (B), U1.8 (GND), U1.19 (GND), U1.20 (GND), U1.22 (GND), U1.49 (GND), U1.60 (GND), U1.71 (GND), U1.72 (GND), U1.81 (GND), U1.92 (GND), U1.104 (AGND), U1.111 (GND), U1.126 (GND), U1.135 (GND), U1.143 (GND), U1.144 (GND), U2.4 (Vss), U3.2 (GND), U3.5 (DIR), U4.3 (GND), U5.2 (GND), U5.5 (DIR), U6.1 (1i), U6.2 (2i), U6.3 (3i), U6.4 (4i), U6.5 (4o), U7.2 (GND), U8.2 (GND), U8.5 (DIR), U9.2 (GND), U10.2 (GND), U11.1 (GND), U11.5 (GND), U11.10 (AGND), U11.11 (GND), U11.13 (TEST), U11.15 (GND), U11.25 (GND), U11.35 (GND), U11.47 (GND), U11.51 (GND), U12.8 (GND), U13.4 (GND), U14.2 (GND), U15.3 (GND), U16.3 (GND), U17.8 (GND), U18.3 (GND), U19.8 (GND), U20.8 (GND), U21.8 (GND), U29.8 (GND), U30.8 (GND), U31.8 (GND), U32.8 (GND), U33.1 (1i), U33.2 (2i), U33.3 (3i), U33.4 (4i), U34.1 (1i), U34.2 (2i), U34.3 (3i), U34.4 (4i), Y1.2, Y1.4, Y2.8 (GND), Y3.2, Y3.4
unnamed: C51.1, R84.2
unnamed: C52.1, R86.2
unnamed: D1.2 (A), R39.1
unnamed: D2.2 (A), R40.1
unnamed: D3.2 (A), R41.1
unnamed: D4.2 (A), R42.1
unnamed: D5.2 (A), R43.2
unnamed: D6.2 (A), R44.2
unnamed: D7.2 (A), R45.2
unnamed: D8.2 (A), R46.2
unnamed: J3.30, R89.2
unnamed: J4.9, R100.1
unnamed: J4.11, R101.1
unnamed: J4.13, R102.1
unnamed: J4.15, R103.1
unnamed: J4.25, R88.1
unnamed: J18.6 (Shield), JP1.2 (B)
unnamed: J19.7 (DAT0), R66.2
unnamed: J19.11 (SHIELD), JP2.2 (B)
unnamed: R35.2, R36.1, R38.1
unnamed: R57.2, U20.5
unnamed: R58.2, U20.2
unnamed: R87.1, U31.3
unnamed: R80.2, U3.3 (A)
unnamed: U4.4, U5.4 (B)
unnamed: R34.2, R70.2, U10.3 (B1)
unnamed: U8.3 (A), U10.1 (B2)
unnamed: R96.1, U11.16 (ADBUS0)
unnamed: R95.1, U11.17 (ADBUS1)
unnamed: R97.1, U11.19 (ADBUS3)
unnamed: R93.1, U11.26 (BDBUS0)
unnamed: R94.1, U11.27 (BDBUS1)
unnamed: R64.1, U11.7 (DM)
unnamed: R65.2, U11.8 (DP)
unnamed: C15.2, U11.2 (OSCI), Y3.3
unnamed: C16.2, U11.3 (OSCO), Y3.1
unnamed: R37.1, U11.6 (REF)
unnamed: R43.1, U12.15 (QA)
unnamed: R39.2, U12.1 (QB)
unnamed: R44.1, U12.2 (QC)
unnamed: R40.2, U12.3 (QD)
unnamed: R45.1, U12.4 (QE)
unnamed: R41.2, U12.5 (QF)
unnamed: R46.1, U12.6 (QG)
unnamed: R42.2, U12.7 (QH)
unnamed: U29.15 (~OE), U30.15 (~OE), U31.15 (~OE), U32.15 (~OE)
unnamed: R25.1, Y2.10 (CLK0)
unnamed: R26.1, Y2.9 (CLK1)
unnamed: R27.1, Y2.6 (CLK2)
unnamed: C4.2, Y1.3, Y2.2 (XA)
unnamed: C5.1, Y1.1, Y2.3 (XB)
VBUS: D11.2 (A2), J18.1 (VBUS), R35.1

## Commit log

2025-10-02 submodule in open source boards
2025-10-02 add packaging/pin border pdf
2025-10-08 add symbol/footprint libs for project
2025-10-08 add hierarchy demo for clock sources
2025-10-08 add schematic for clock generator, some symbols
2025-10-09 update signal supporting ckts
2025-10-10 clean up supporting blocks; add nucleo symbol
2025-10-15 Init daughter board
2025-10-20 move daughterboard to subprj folder
2025-10-20 add footprints for signal conditioning
2025-10-22 update motheboard schems to include conn
2025-10-22 in-class work at schems
2025-10-23 clean up some pull up/downs
2025-10-24 add jlc stackup, size pulldowns
2025-10-25 rough layout stufF
2025-10-26 add mezzanine symbol/footprint, init daughterboard placement
2025-10-26 daughter placement v1, add 3D models for mezzanine + uFL
2025-10-26 update uFL 3D model
2025-10-27 Added most of nucleo domain to the motherboard schematic
2025-10-27 resaved maybe more updates on the motherboard schematic
2025-10-27 Added the irq and irq2 inputs to the nucleo
2025-10-27 Added the rest of the ports
2025-10-27 add 3D models with rel paths, add stitching via footprint, update daughter pcb schematic
2025-10-27 begin routing daughterboard
2025-10-31 clean up schematics, add proper connectors
2025-11-01 update ftdi chip
2025-11-01 combine hierarchy of all sans power
2025-11-01 add some daughterboard routing
2025-11-02 more daughterboard routing
2025-11-03 scoreboard! scoreboard! wait... what?
2025-11-03 current monitor symbol
2025-11-03 daughterboard routing, changed some mezzanine pins - more to come
2025-11-03 partial update to use STM board, updated muxing of FTDI
2025-11-03 working through switching
2025-11-05 pmic switching schem done
2025-11-05 update FTDI interfacing
2025-11-05 complete signal routing on daughterboard, TODO: power/gnd connections
2025-11-05 2V5 LDO symbol in its own dir
2025-11-07 add JLC part num for parts, footprints
2025-11-07 messing around with floorplanning
2025-11-08 update footprints, final
2025-11-10 more daughterboard routing, power focus
2025-11-10 update motherboard floorplanning
2025-11-10 daughterboard routing, 90% done
2025-11-10 add aux SPI dual-master to drive caravel CPU
2025-11-10 2V5 added to part lib (again?), supplies schem done?
2025-11-10 note on bypass cap on schem
2025-11-10 finish daughter routing + silk
2025-11-10 fuses, ferrite bead, 5V0 selection connector
2025-11-10 supply connectors, solder bridges
2025-11-10 prettied switching schem
2025-11-10 fuse, fb info in values
2025-11-10 prettied supplies schem
2025-11-10 john's notes
2025-11-10 map to STM pins
2025-11-11 updates to routing
2025-11-11 add qfn small epad footprint, update silk on daughterboard, add fiducials, adjust mezzanine spacing
2025-11-11 more routing progress, add termination resistors
2025-11-12 finalize termination
2025-11-12 update jlcpcb part numbers
2025-11-12 core routing progress
2025-11-12 pins out progress
2025-11-12 add FTDI local routing, muxes
2025-11-12 need to map mthrbrd to nucleo + doc online
2025-11-13 further routing progess: core routing done
2025-11-17 complete routing for core
2025-11-17 halfway done routing to edge, next is analog header, gnd
2025-11-17 add MH for orientation indicator
2025-11-17 update gitignore for gerbers
2025-11-17 will it conflict?
2025-12-02 can't work on one machine
2025-12-03 check in
2025-12-10 no erc errors but on root

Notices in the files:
592-kicad-pcb/sky130_nfc_daughter/sky130_nfc_daughter.kicad_pcb:
(C) 2025, Alexander Gershman
